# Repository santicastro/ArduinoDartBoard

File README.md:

ArduinoDartsBoard
=================

Electronic darts board controlled by Arduino Mini Pro. It's o a very early development status. Only cricket game is implemented and has some bugs.

I built the software and the pcb from scratch. I'll upload the pcb diagrams as soon as I can.

Sample of the game finished melody: http://www.youtube.com/watch?v=AD7XjPF0V5o

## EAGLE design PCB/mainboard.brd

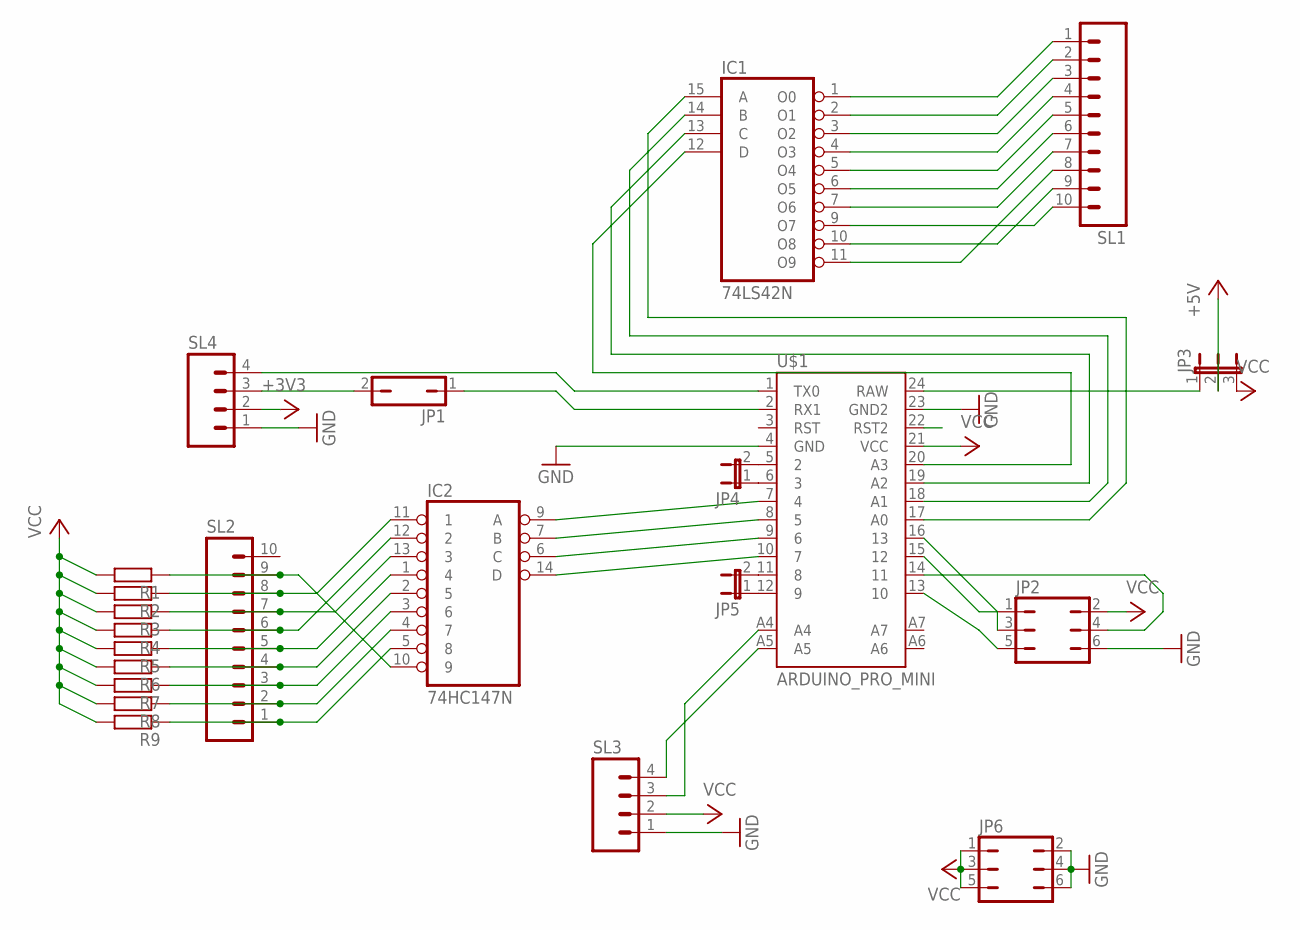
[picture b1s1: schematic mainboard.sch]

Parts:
IC1: 74LS42N; DIL16
IC2: 74HC147N; DIL16
JP1: JP1Q; JP1
JP2, JP6: JP3Q
JP3: JP2E; JP2
JP4, JP5: JP1E; JP1
R1, R2, R3, R4, R5, R6, R7, R8, R9: R-EU_0204/7; 0204/7
SL1, SL2: M10; 10P
SL3, SL4: M04; 04P
U$1: ARDUINO_PRO_MINI

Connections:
+3V3: SL4.2
+5V: JP3.2
GND: IC1.8 (GND), IC2.8 (GND), JP2.6, JP6.2, JP6.4, JP6.6, SL3.1, SL4.1, U$1.4 (GND), U$1.23 (GND2)
unnamed: IC2.2 (5), R6.1, SL2.4
unnamed: IC2.1 (4), R5.1, SL2.5
unnamed: IC2.12 (2), R4.1, SL2.6
unnamed: IC2.5 (8), R9.1, SL2.1
unnamed: IC2.4 (7), R8.1, SL2.2
unnamed: IC2.3 (6), R7.1, SL2.3
unnamed: IC2.13 (3), R3.1, SL2.7
unnamed: IC2.11 (1), R2.1, SL2.8
unnamed: IC2.10 (9), R1.1, SL2.9
unnamed: IC1.15 (A), U$1.17 (A0)
unnamed: IC1.14 (B), U$1.18 (A1)
unnamed: IC1.13 (C), U$1.19 (A2)
unnamed: IC1.12 (D), U$1.20 (A3)
unnamed: IC1.9 (O7), SL1.10
unnamed: IC1.10 (O8), SL1.9
unnamed: IC1.11 (O9), SL1.8
unnamed: IC2.9 (A), U$1.7 (4)
unnamed: IC1.1 (O0), SL1.1
unnamed: IC1.2 (O1), SL1.2
unnamed: IC1.3 (O2), SL1.3
unnamed: IC1.4 (O3), SL1.4
unnamed: IC1.5 (O4), SL1.5
unnamed: IC1.6 (O5), SL1.6
unnamed: IC1.7 (O6), SL1.7
unnamed: IC2.7 (B), U$1.8 (5)
unnamed: IC2.6 (C), U$1.9 (6)
unnamed: IC2.14 (D), U$1.10 (7)
unnamed: SL3.4, U$1.A5
unnamed: SL3.3, U$1.A4
unnamed: SL4.4, U$1.1 (TX0)
unnamed: JP1.2, SL4.3
unnamed: JP1.1, U$1.2 (RX1)
unnamed: JP2.1, U$1.15 (12)
unnamed: JP2.3, U$1.16 (13)
unnamed: JP2.5, U$1.13 (10)
unnamed: JP2.4, U$1.14 (11)
unnamed: JP3.1, U$1.24 (RAW)
unnamed: JP4.1, U$1.6 (3)
unnamed: JP4.2, U$1.5 (2)
unnamed: JP5.1, U$1.12 (9)
unnamed: JP5.2, U$1.11 (8)
VCC: IC1.16 (VCC), IC2.16 (VCC), JP2.2, JP3.3, JP6.1, JP6.3, JP6.5, R1.2, R2.2, R3.2, R4.2, R5.2, R6.2, R7.2, R8.2, R9.2, SL3.2, U$1.21 (VCC)

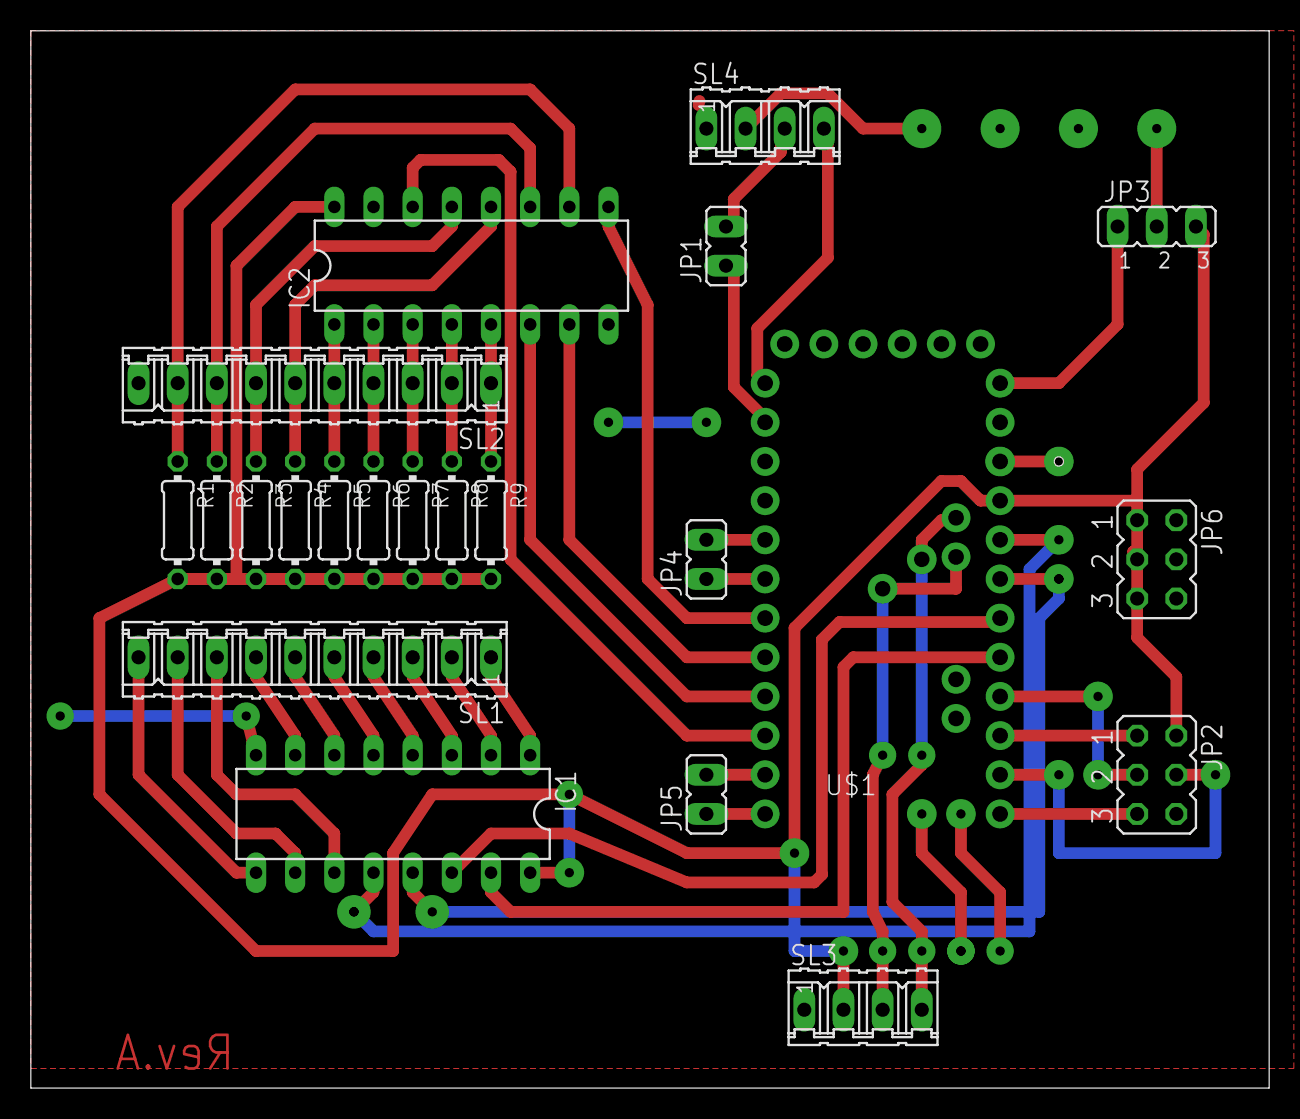
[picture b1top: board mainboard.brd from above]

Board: 2 copper layers, 80.3 x 68.6 mm, 22 parts (0 on the bottom side), 43 nets.

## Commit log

2013-08-16 Initial code
2013-08-16 Images replaced
2013-08-17 Added pcb design
2013-08-19 Modified sketch

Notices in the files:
parts and their libraries:
SparkFun-Boards: Licensing: CC v3.0 Share-Alike You are welcome to use this library for commercial purposes.
